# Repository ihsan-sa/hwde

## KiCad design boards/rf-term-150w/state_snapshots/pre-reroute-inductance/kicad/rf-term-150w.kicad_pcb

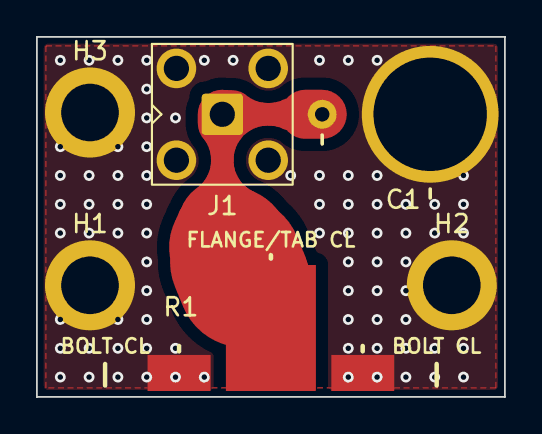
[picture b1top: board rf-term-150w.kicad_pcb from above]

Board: 2 copper layers, 26.0 x 20.0 mm, 6 parts (0 on the bottom side), 2 nets.

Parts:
C1: 1-30pF; CAP-ADJ-TH_2P-BD7.5_5602
H1, H2, H3: M3; MountingHole_3.2mm_M3_Pad_5.0mm
J1: SMA; SMA_BAT_Wireless_BWSMA-KWE-Z001
R1: 50R 250W; R_LapPad_T50R0-250-12X

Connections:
/RF: C1.2, J1.1, R1.1
GND: C1.1, H1.1, H2.1, H3.1, J1.2, R1.2

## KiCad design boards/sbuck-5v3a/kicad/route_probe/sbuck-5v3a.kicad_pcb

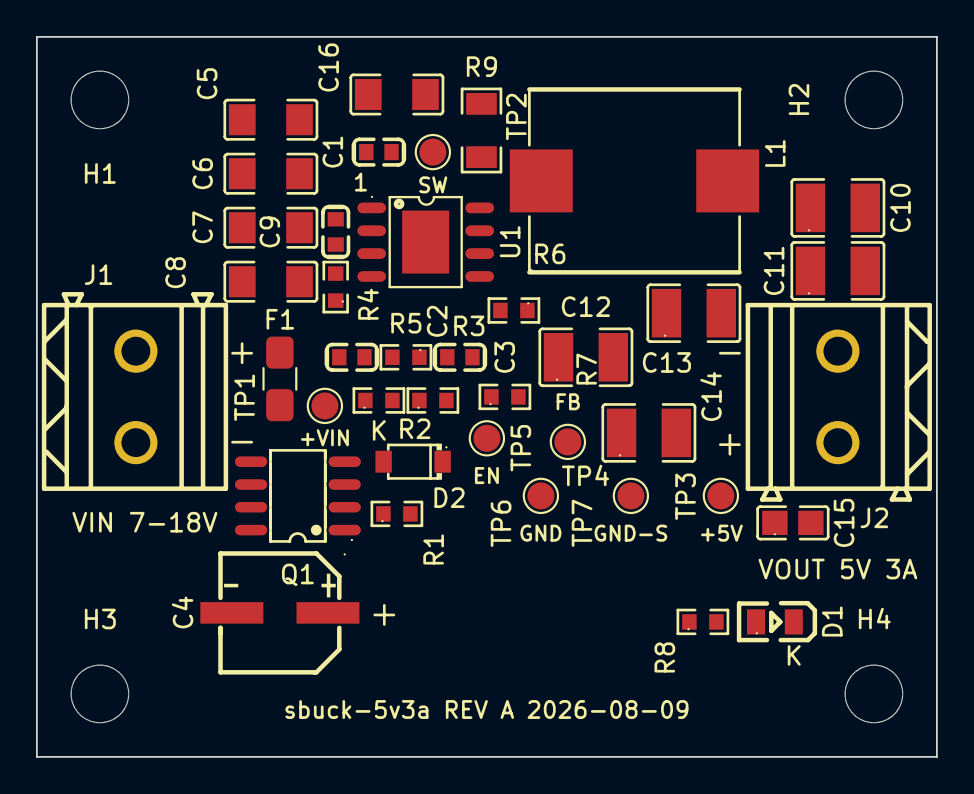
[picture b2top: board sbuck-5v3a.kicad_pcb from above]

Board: 4 copper layers, 50.0 x 40.0 mm, 44 parts (0 on the bottom side), 15 nets, no tracks yet.

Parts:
C1, C9: 100nF 50V X7R; C0603
C2: 3.3nF 50V X7R; C0603
C3: 10pF 50V C0G; C0603
C4: 100uF 35V 80mOhm; CAP-SMD_BD6.3-L6.5-W6.5-LS7.2-FD
C5, C6, C7, C8: 4.7uF 50V X7R; C1206
C10, C11, C12, C13, C14: 22uF 25V X7R; C1210
C15: 4.7uF 16V X7R; C0805
C16: 470pF 1kV C0G; C1206
D1: GREEN; LED0805-R-RD
D2: BZT52C15 15V; SOD-123_L2.7-W1.6-LS3.7-RD
F1: 5A slow-blow; Fuse_1206_C1T_BelVendorLand
H1, H2, H3, H4: M3_3.2mm; MountingHole_3.2mm_M3
J1, J2: SCREW_5.08_2P; CONN-TH_2P-P5.08_DB128L-5.08-2P
L1: 6.8uH; IND-SMD_L11.5-W10.0
Q1: AO4407A; SOIC-8_L4.9-W3.9-P1.27-LS6.0-BL
R1: 100k 1%; R0603
R2: 105k 1%; R0603
R3: 24.0k 1%; R0603
R4: 200k 1%; R0603
R5: 75k 1%; R0603
R6: 105k 0.1%; R0603
R7: 20.0k 0.1%; R0603
R8: 2.2k 1%; R0603
R9: 22R 1% 0.25W; R1206
TP1: +VIN; TestPoint_Pad_D1.5mm
TP2: SW; TestPoint_Pad_D1.5mm
TP3: +5V; TestPoint_Pad_D1.5mm
TP4: FB; TestPoint_Pad_D1.5mm
TP5: EN; TestPoint_Pad_D1.5mm
TP6, TP7: GND; TestPoint_Pad_D1.5mm
U1: AP64350SP-13; SO-8_L4.9-W3.9-P1.27-LS6.0-BL-EP

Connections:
+5V: C10.1, C11.1, C12.1, C13.1, C14.1, C15.1, J2.1, L1.2, R6.1, R8.1, TP3.1
+VIN: C4.1, C5.1, C6.1, C7.1, C8.1, C9.1, D2.1, Q1.1, Q1.2, Q1.3, R2.1, TP1.1, U1.2
/BST: C1.1, U1.1
/COMP: C3.1, R5.1, U1.6
/COMPZ: C2.1, R5.2
/EN: R2.2, R3.1, TP5.1, U1.3
/FB: R6.2, R7.1, TP4.1, U1.5
/LEDA: D1.1, R8.2
/QGATE: D2.2, Q1.4, R1.1
/RT: R4.1, U1.4
/SNUBZ: C16.1, R9.2
/SW: C1.2, L1.1, R9.1, TP2.1, U1.8
/VIN: F1.2, Q1.5, Q1.6, Q1.7, Q1.8
/VIN_RAW: F1.1, J1.1
GND: C2.2, C3.2, C4.2, C5.2, C6.2, C7.2, C8.2, C9.2, C10.2, C11.2, C12.2, C13.2, C14.2, C15.2, C16.2, D1.2, J1.2, J2.2, R1.2, R3.2, R4.2, R7.2, TP6.1, TP7.1, U1.7, U1.9
